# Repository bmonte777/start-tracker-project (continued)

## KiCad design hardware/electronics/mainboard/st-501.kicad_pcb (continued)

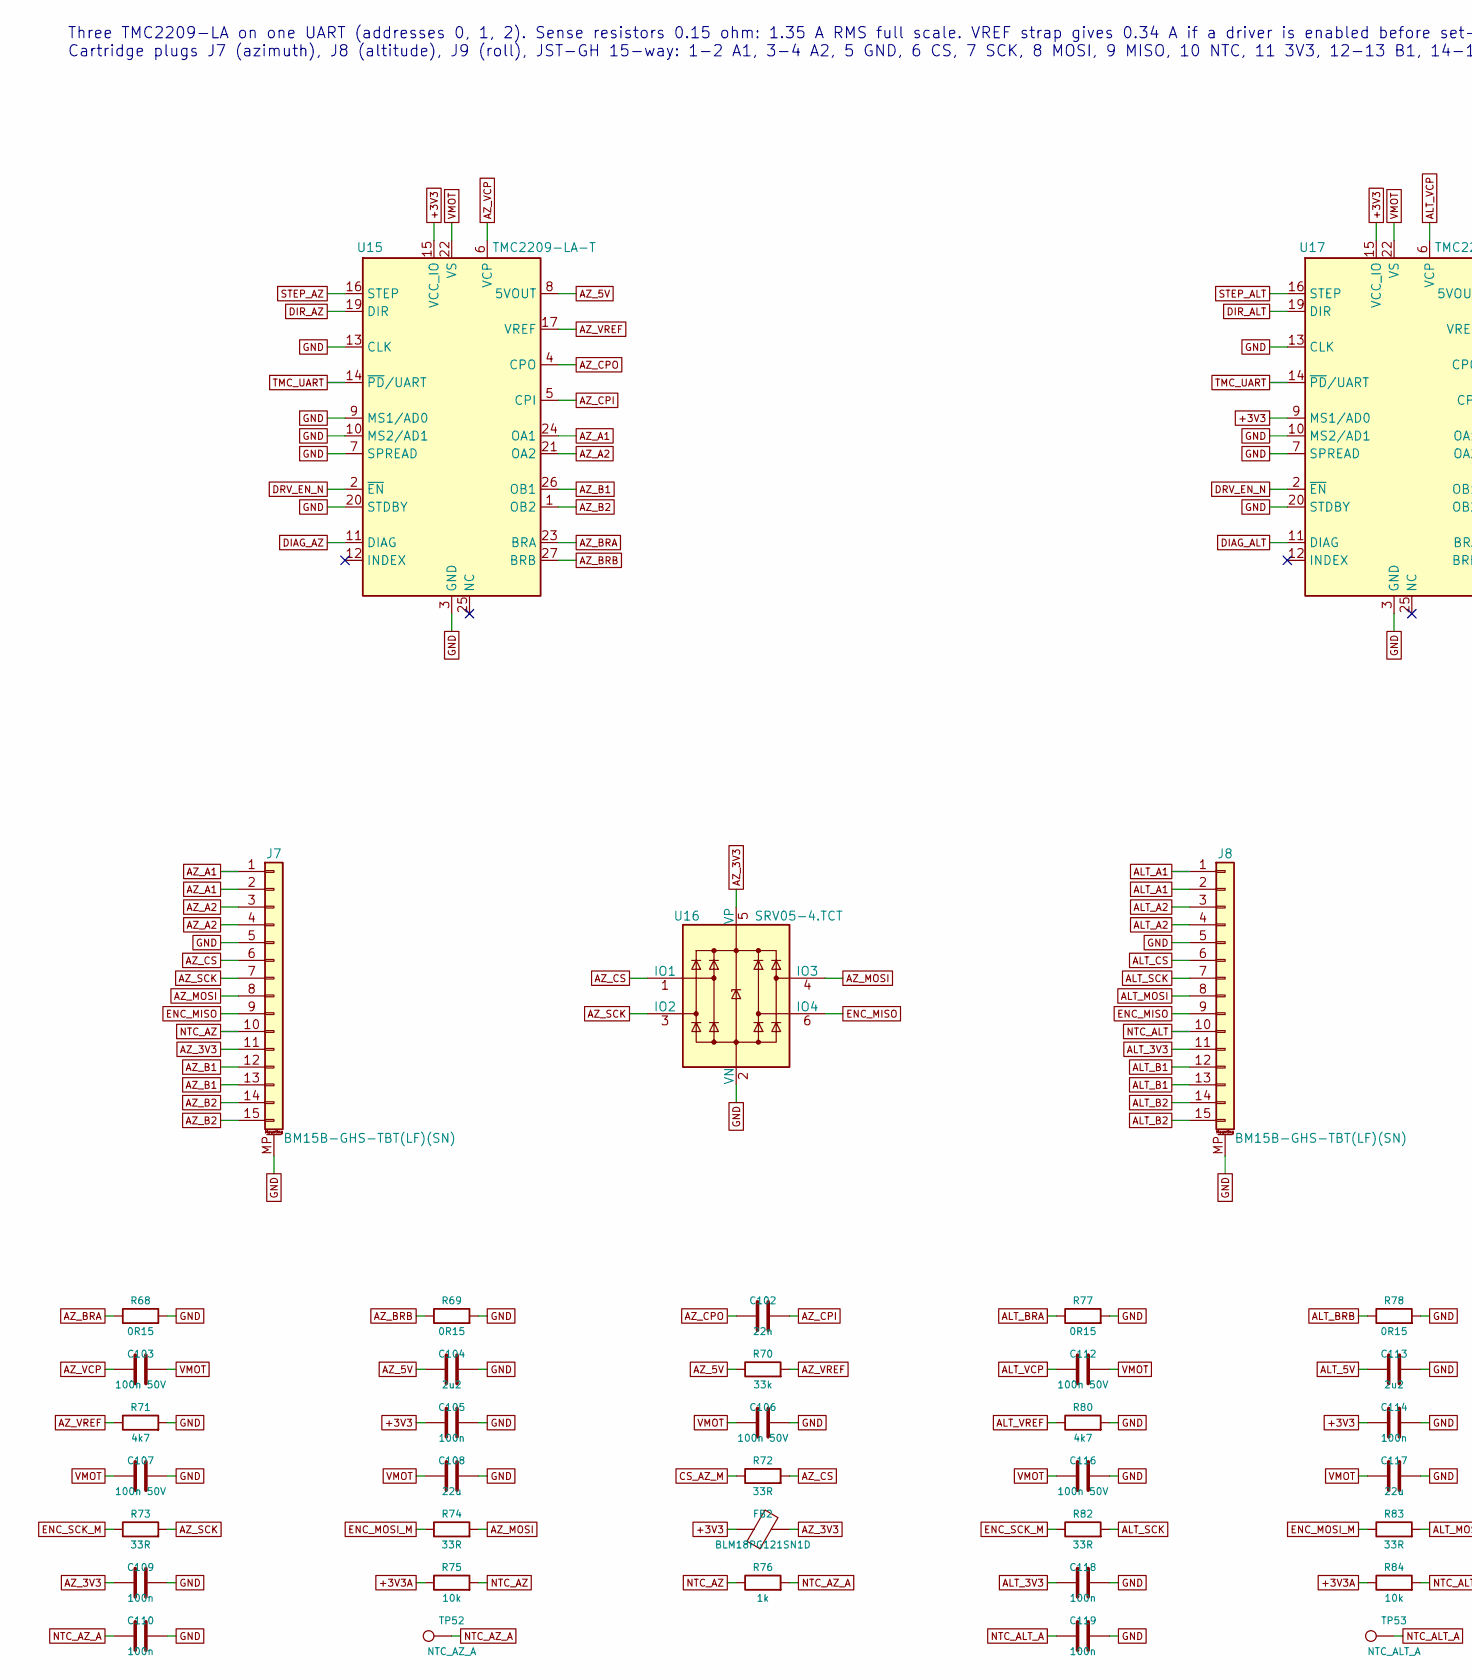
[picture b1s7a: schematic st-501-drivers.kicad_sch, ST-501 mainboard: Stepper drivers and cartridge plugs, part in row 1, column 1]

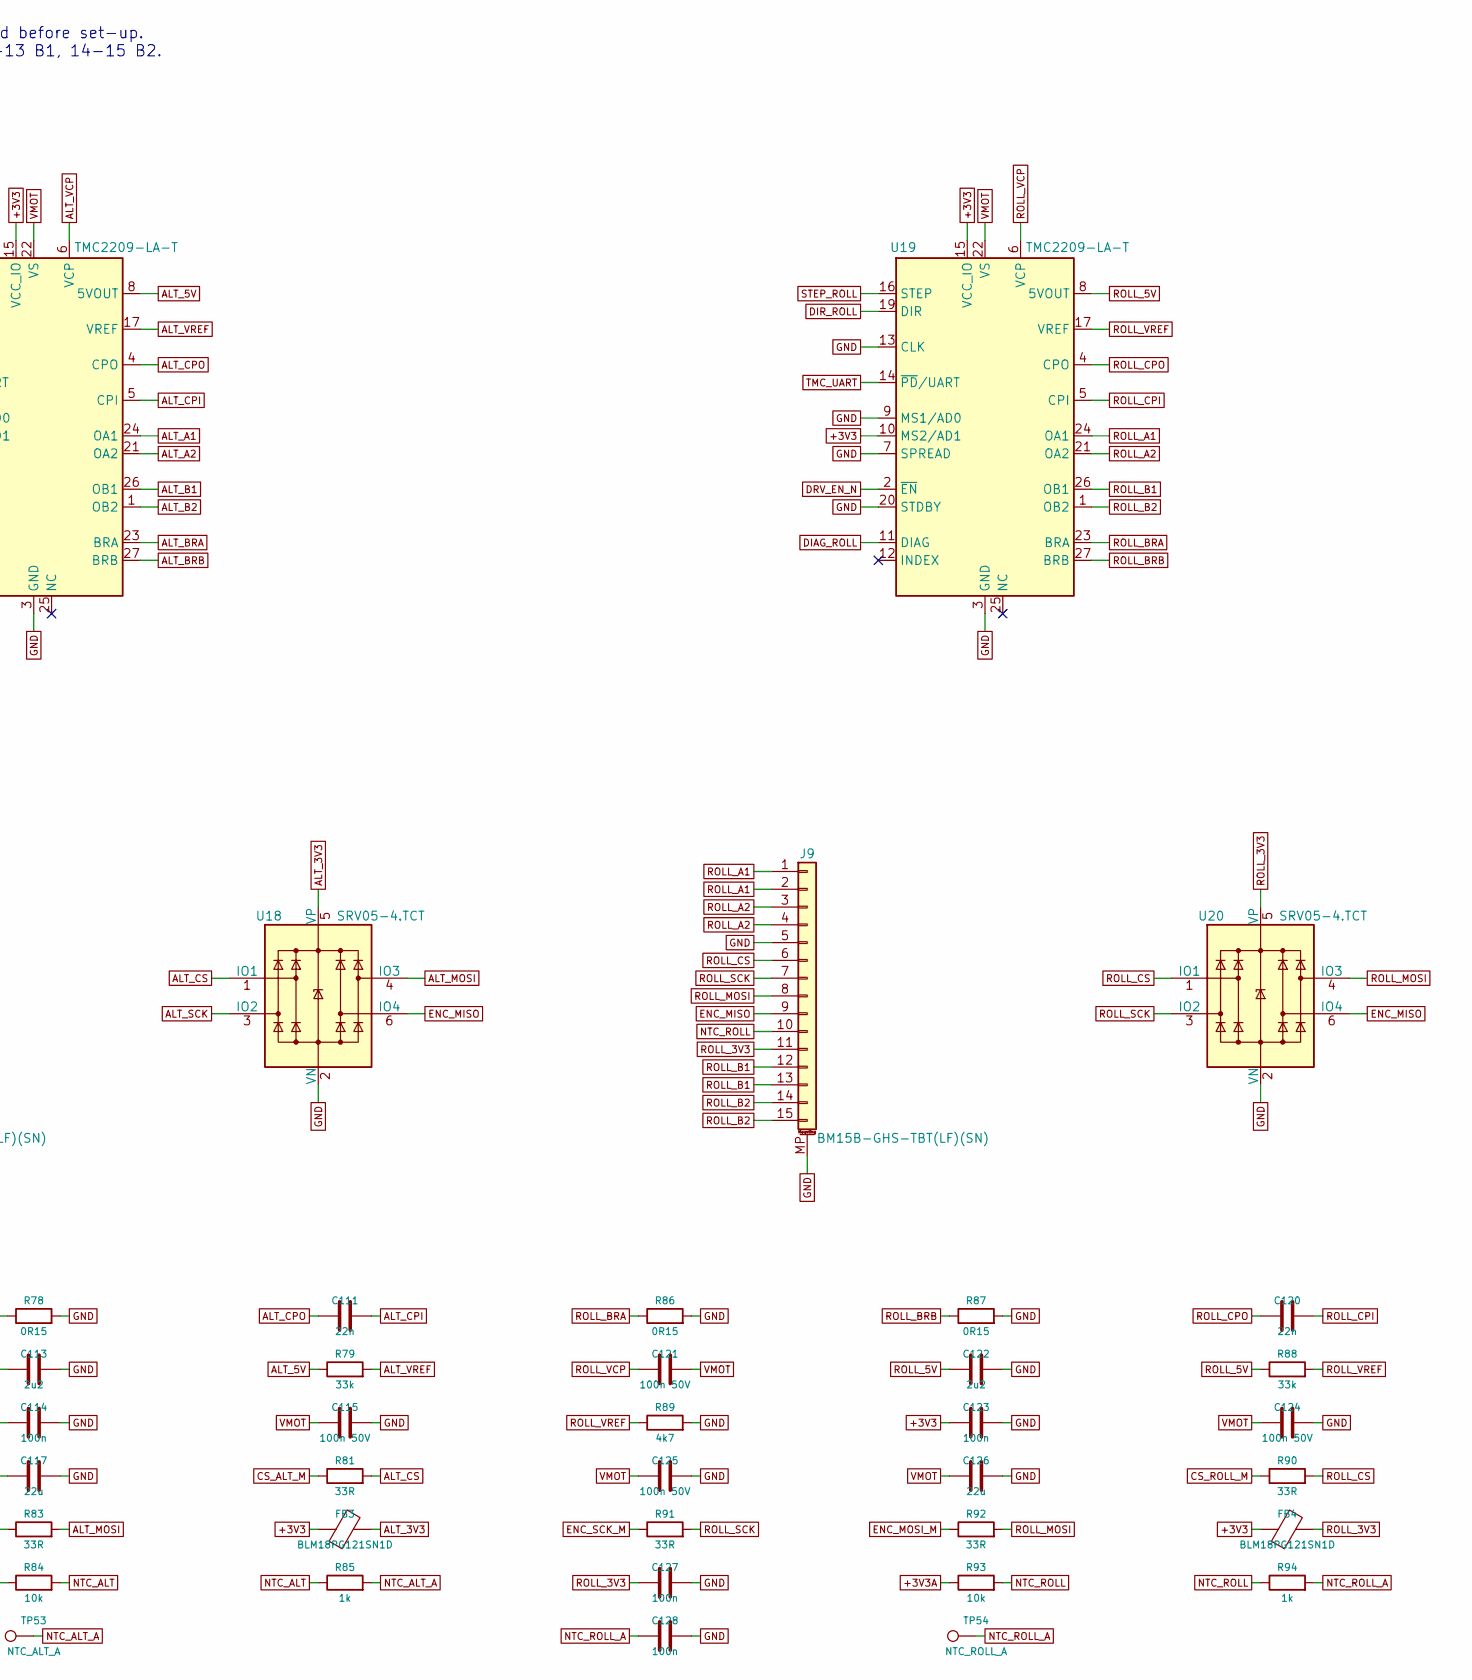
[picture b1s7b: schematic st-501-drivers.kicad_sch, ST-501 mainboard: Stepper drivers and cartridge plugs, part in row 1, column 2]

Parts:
C102, C111, C120: 22n; C_0402_1005Metric; MPN CL05B223KB5NNNC; LCSC C1532
C103, C106, C107, C112, C115, C116, C121, C124, C125: 100n 50V; C_0402_1005Metric; MPN CL05B104KB54PNC; LCSC C307331
C104, C113, C122: 2u2; C_0603_1608Metric; MPN CL10A225KO8NNNC; LCSC C23630
C105, C109, C110, C114, C118, C119, C123, C127, C128: 100n; C_0402_1005Metric; MPN CL05B104KO5NNNC; LCSC C1525
C108, C117, C126: 22u; C_0805_2012Metric; MPN CL21A226MAQNNNE; LCSC C45783
FB2, FB3, FB4: BLM18PG121SN1D; L_0603_1608Metric; MPN BLM18PG121SN1D; LCSC C14709
J7, J8, J9: BM15B-GHS-TBT(LF)(SN); JST_GH_BM15B-GHS-TBT_1x15-1MP_P1.25mm_Vertical_3D; MPN BM15B-GHS-TBT(LF)(SN); LCSC C5305069
R68, R69, R77, R78, R86, R87: 0R15; R_1206_3216Metric; MPN 0.15 ohm 1 % 0.5 W current sense
R70, R79, R88: 33k; R_0402_1005Metric; MPN 0402WGF3302TCE; LCSC C25779
R71, R80, R89: 4k7; R_0402_1005Metric; MPN 0402WGF4701TCE; LCSC C25900
R72, R73, R74, R81, R82, R83, R90, R91, R92: 33R; R_0402_1005Metric; MPN 0402WGF330JTCE; LCSC C25105
R75, R84, R93: 10k; R_0402_1005Metric; MPN 0402WGF1002TCE; LCSC C25744
R76, R85, R94: 1k; R_0402_1005Metric; MPN 0402WGF1001TCE; LCSC C11702
TP52: NTC_AZ_A; TestPoint_Pad_D1.0mm
TP53: NTC_ALT_A; TestPoint_Pad_D1.0mm
TP54: NTC_ROLL_A; TestPoint_Pad_D1.0mm
U15, U17, U19: TMC2209-LA-T; VQFN-28-1EP_5x5mm_P0.5mm_EP3.7x3.7mm_ThermalVias; MPN TMC2209-LA-T; LCSC C465949
U16, U18, U20: SRV05-4.TCT; SOT-23-6; MPN SRV05-4.TCT; LCSC C2687126

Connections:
+3V3: C105.1, C114.1, C123.1, FB2.1, FB3.1, FB4.1, U15.15 (VCC_IO), U17.9 (MS1/AD0), U17.15 (VCC_IO), U19.10 (MS2/AD1), U19.15 (VCC_IO); also elsewhere on the board
+3V3A: R75.1, R84.1, R93.1; also elsewhere on the board
ALT_3V3: C118.1, FB3.2, J8.11, U18.5 (VP)
ALT_5V: C113.1, R79.1, U17.8 (5VOUT)
ALT_A1: J8.1, J8.2, U17.24 (OA1)
ALT_A2: J8.3, J8.4, U17.21 (OA2)
ALT_B1: J8.12, J8.13, U17.26 (OB1)
ALT_B2: J8.14, J8.15, U17.1 (OB2)
ALT_BRA: R77.1, U17.23 (BRA)
ALT_BRB: R78.1, U17.27 (BRB)
ALT_CPI: C111.2, U17.5 (CPI)
ALT_CPO: C111.1, U17.4 (CPO)
ALT_CS: J8.6, R81.2, U18.1 (IO1)
ALT_MOSI: J8.8, R83.2, U18.4 (IO3)
ALT_SCK: J8.7, R82.2, U18.3 (IO2)
ALT_VCP: C112.1, U17.6 (VCP)
ALT_VREF: R79.2, R80.1, U17.17 (VREF)
AZ_3V3: C109.1, FB2.2, J7.11, U16.5 (VP)
AZ_5V: C104.1, R70.1, U15.8 (5VOUT)
AZ_A1: J7.1, J7.2, U15.24 (OA1)
AZ_A2: J7.3, J7.4, U15.21 (OA2)
AZ_B1: J7.12, J7.13, U15.26 (OB1)
AZ_B2: J7.14, J7.15, U15.1 (OB2)
AZ_BRA: R68.1, U15.23 (BRA)
AZ_BRB: R69.1, U15.27 (BRB)
AZ_CPI: C102.2, U15.5 (CPI)
AZ_CPO: C102.1, U15.4 (CPO)
AZ_CS: J7.6, R72.2, U16.1 (IO1)
AZ_MOSI: J7.8, R74.2, U16.4 (IO3)
AZ_SCK: J7.7, R73.2, U16.3 (IO2)
AZ_VCP: C103.1, U15.6 (VCP)
AZ_VREF: R70.2, R71.1, U15.17 (VREF)
CS_ALT_M: R81.1; also elsewhere on the board
CS_AZ_M: R72.1; also elsewhere on the board
CS_ROLL_M: R90.1; also elsewhere on the board
DIAG_ALT: U17.11 (DIAG); also elsewhere on the board
DIAG_AZ: U15.11 (DIAG); also elsewhere on the board
DIAG_ROLL: U19.11 (DIAG); also elsewhere on the board
DIR_ALT: U17.19 (DIR); also elsewhere on the board
DIR_AZ: U15.19 (DIR); also elsewhere on the board
DIR_ROLL: U19.19 (DIR); also elsewhere on the board
DRV_EN_N: U15.2 (~EN), U17.2 (~EN), U19.2 (~EN); also elsewhere on the board
ENC_MISO: J7.9, J8.9, J9.9, U16.6 (IO4), U18.6 (IO4), U20.6 (IO4); also elsewhere on the board
ENC_MOSI_M: R74.1, R83.1, R92.1; also elsewhere on the board
ENC_SCK_M: R73.1, R82.1, R91.1; also elsewhere on the board
GND: C104.2, C105.2, C106.2, C107.2, C108.2, C109.2, C110.2, C113.2, C114.2, C115.2, C116.2, C117.2, C118.2, C119.2, C122.2, C123.2, C124.2, C125.2, C126.2, C127.2, C128.2, J7.5, J7.MP (MountPin), J8.5, J8.MP (MountPin), J9.5, J9.MP (MountPin), R68.2, R69.2, R71.2, R77.2, R78.2, R80.2, R86.2, R87.2, R89.2, U15.3 (GND), U15.7 (SPREAD), U15.9 (MS1/AD0), U15.10 (MS2/AD1), U15.13 (CLK), U15.18 (GND), U15.20 (STDBY), U15.29 (GND), U16.2 (VN), U17.3 (GND), U17.7 (SPREAD), U17.10 (MS2/AD1), U17.13 (CLK), U17.18 (GND), U17.20 (STDBY), U17.29 (GND), U18.2 (VN), U19.3 (GND), U19.7 (SPREAD), U19.9 (MS1/AD0), U19.13 (CLK), U19.18 (GND), U19.20 (STDBY), U19.29 (GND), U20.2 (VN); also elsewhere on the board
NTC_ALT: J8.10, R84.2, R85.1
NTC_ALT_A: C119.1, R85.2, TP53.1; also elsewhere on the board
NTC_AZ: J7.10, R75.2, R76.1
NTC_AZ_A: C110.1, R76.2, TP52.1; also elsewhere on the board
NTC_ROLL: J9.10, R93.2, R94.1
NTC_ROLL_A: C128.1, R94.2, TP54.1; also elsewhere on the board
ROLL_3V3: C127.1, FB4.2, J9.11, U20.5 (VP)
ROLL_5V: C122.1, R88.1, U19.8 (5VOUT)
ROLL_A1: J9.1, J9.2, U19.24 (OA1)
ROLL_A2: J9.3, J9.4, U19.21 (OA2)
ROLL_B1: J9.12, J9.13, U19.26 (OB1)
ROLL_B2: J9.14, J9.15, U19.1 (OB2)
ROLL_BRA: R86.1, U19.23 (BRA)
ROLL_BRB: R87.1, U19.27 (BRB)
ROLL_CPI: C120.2, U19.5 (CPI)
ROLL_CPO: C120.1, U19.4 (CPO)
ROLL_CS: J9.6, R90.2, U20.1 (IO1)
ROLL_MOSI: J9.8, R92.2, U20.4 (IO3)
ROLL_SCK: J9.7, R91.2, U20.3 (IO2)
ROLL_VCP: C121.1, U19.6 (VCP)
ROLL_VREF: R88.2, R89.1, U19.17 (VREF)
STEP_ALT: U17.16 (STEP); also elsewhere on the board
STEP_AZ: U15.16 (STEP); also elsewhere on the board
STEP_ROLL: U19.16 (STEP); also elsewhere on the board
TMC_UART: U15.14 (~PD/UART), U17.14 (~PD/UART), U19.14 (~PD/UART); also elsewhere on the board
VMOT: C103.2, C106.1, C107.1, C108.1, C112.2, C115.1, C116.1, C117.1, C121.2, C124.1, C125.1, C126.1, U15.22 (VS), U15.28 (VS), U17.22 (VS), U17.28 (VS), U19.22 (VS), U19.28 (VS); also elsewhere on the board

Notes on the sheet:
Three TMC2209-LA on one UART (addresses 0, 1, 2). Sense resistors 0.15 ohm: 1.35 A RMS full scale. VREF strap gives 0.34 A if a driver is enabled before set-up. Cartridge plugs J7 (azimuth), J8 (altitude), J9 (roll), JST-GH 15-way: 1-2 A1, 3-4 A2, 5 GND, 6 CS, 7 SCK, 8 MOSI, 9 MISO, 10 NTC, 11 3V3,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

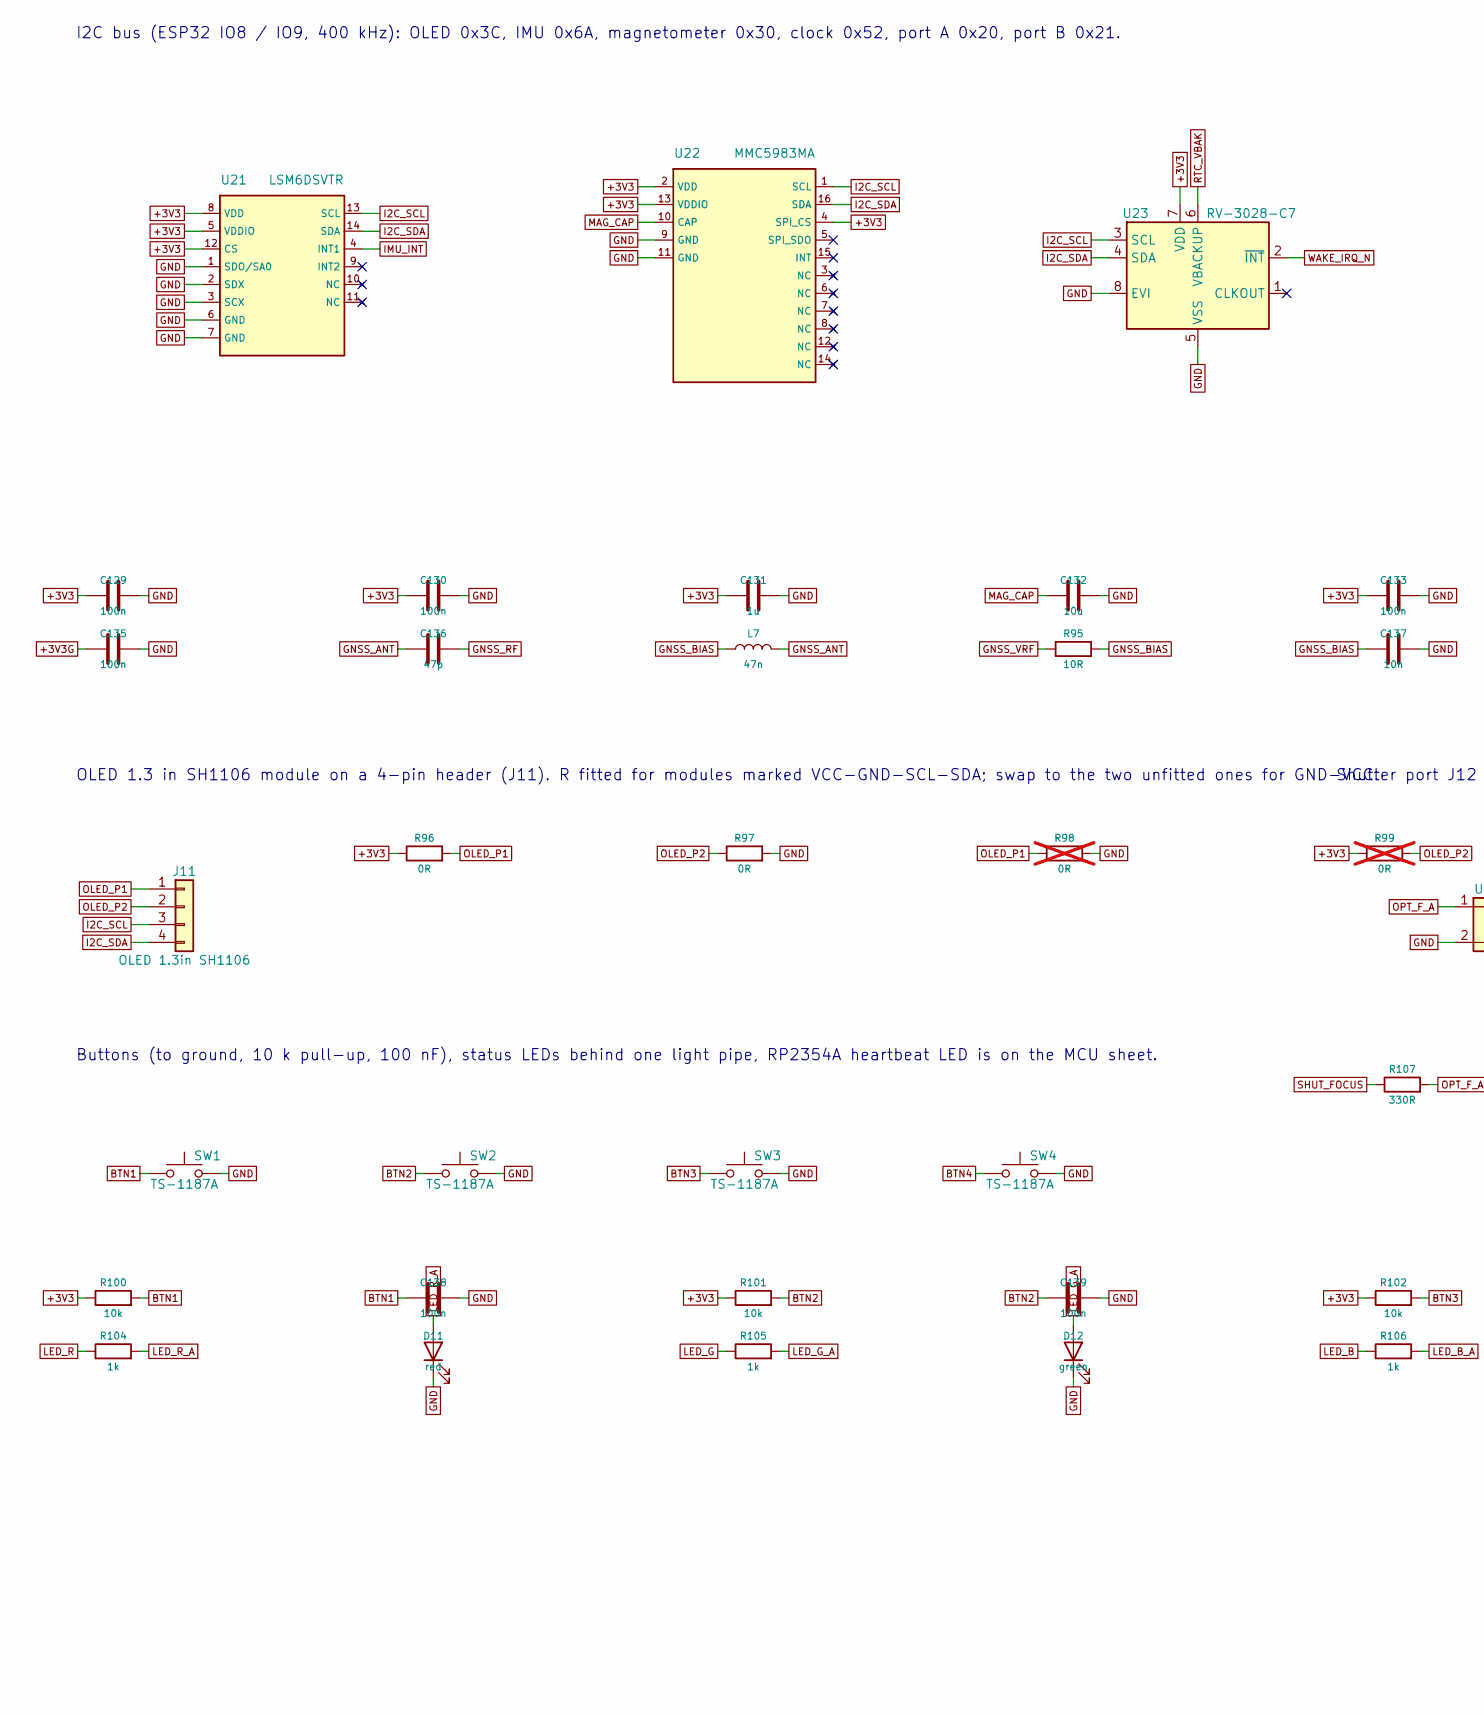
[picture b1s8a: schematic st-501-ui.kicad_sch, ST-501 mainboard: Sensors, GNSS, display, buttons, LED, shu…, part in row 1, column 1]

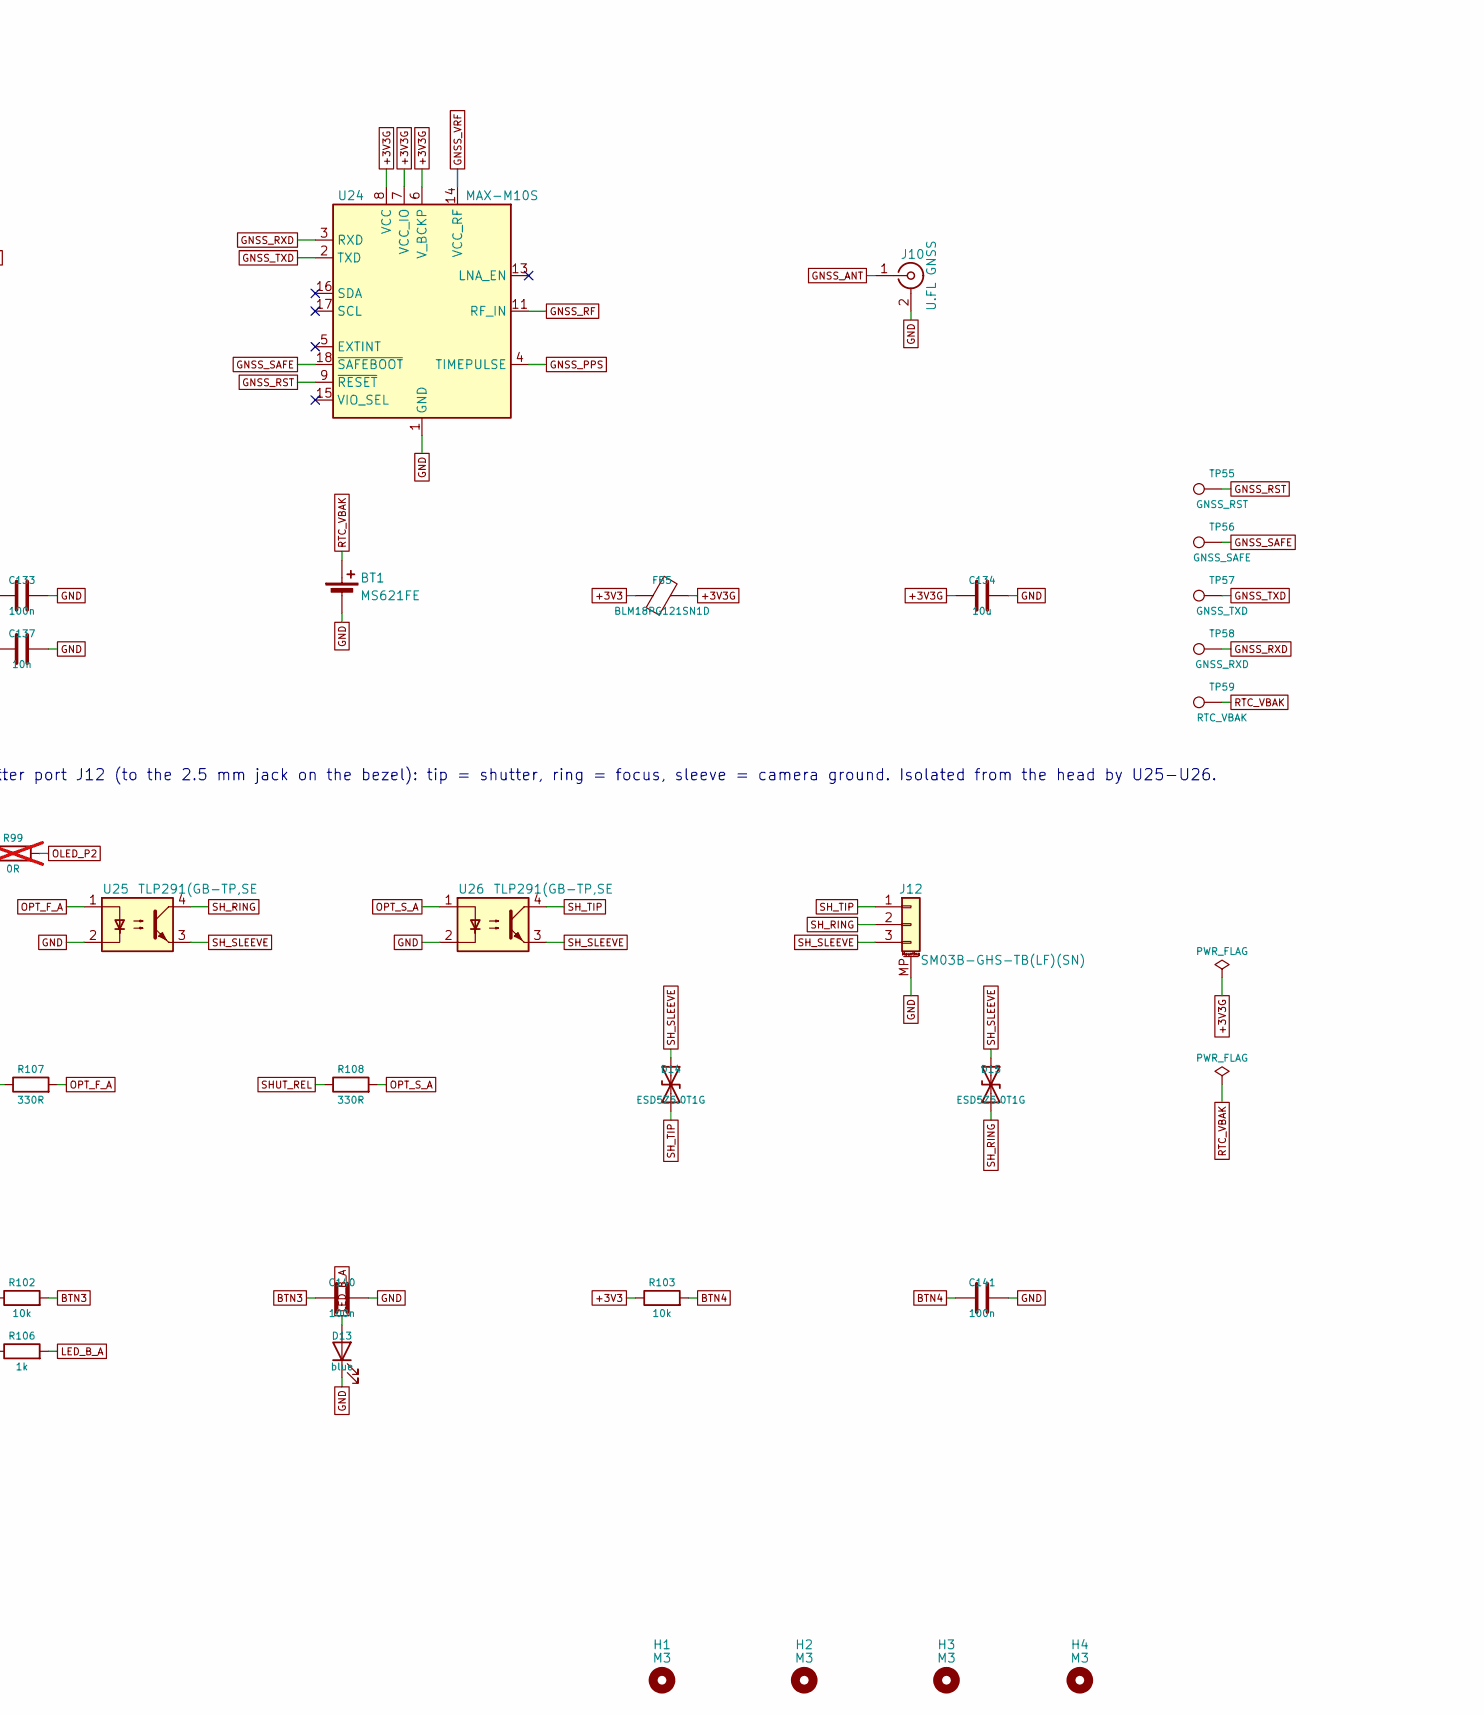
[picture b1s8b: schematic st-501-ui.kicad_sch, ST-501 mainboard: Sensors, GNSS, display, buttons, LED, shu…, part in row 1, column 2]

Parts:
BT1: MS621FE; BatteryHolder_Seiko_MS621F; MPN MS621FE-FL11E
C129, C130, C133, C135, C138, C139, C140, C141: 100n; C_0402_1005Metric; MPN CL05B104KO5NNNC; LCSC C1525
C131: 1u; C_0402_1005Metric; MPN CL05A105KA5NQNC; LCSC C52923
C132, C134: 10u; C_0603_1608Metric; MPN CL10A106KP8NNNC; LCSC C19702
C136: 47p; C_0402_1005Metric; MPN 0402CG470J500NT; LCSC C1567
C137: 10n; C_0402_1005Metric; MPN CL05B103KB5NNNC; LCSC C15195
D11: red; LED_0603_1608Metric; MPN KT-0603R; LCSC C2286
D12: green; LED_0603_1608Metric; MPN 19-217/GHC-YR1S2/3T; LCSC C72043
D13: blue; LED_0603_1608Metric; MPN 19-217/BHC-ZL1M2RY/3T; LCSC C72041
D14, D15: ESD5Z5.0T1G; D_SOD-523; MPN ESD5Z5.0T1G
FB5: BLM18PG121SN1D; L_0603_1608Metric; MPN BLM18PG121SN1D; LCSC C14709
H1, H2, H3, H4: M3; MountingHole_3.2mm_M3_ISO7380
J10: U.FL GNSS; U.FL_Hirose_U.FL-R-SMT-1_Vertical; MPN U.FL-R-SMT-1(80); LCSC C88374
J11: OLED 1.3in SH1106; PinHeader_1x04_P2.54mm_Vertical
J12: SM03B-GHS-TB(LF)(SN); JST_GH_SM03B-GHS-TB_1x03-1MP_P1.25mm_Horizontal; MPN SM03B-GHS-TB(LF)(SN); LCSC C514175
L7: 47n; L_0402_1005Metric; MPN LQG15HS47NJ02D; LCSC C97998
R95: 10R; R_0402_1005Metric; MPN 0402WGF100JTCE; LCSC C25077
R96, R97: 0R; R_0402_1005Metric; MPN 0402WGF0000TCE; LCSC C17168
R98, R99: 0R; R_0402_1005Metric; MPN 0402WGF0000TCE; LCSC C17168; not fitted
R100, R101, R102, R103: 10k; R_0402_1005Metric; MPN 0402WGF1002TCE; LCSC C25744
R104, R105, R106: 1k; R_0402_1005Metric; MPN 0402WGF1001TCE; LCSC C11702
R107, R108: 330R; R_0402_1005Metric; MPN 0402WGF3300TCE; LCSC C25104
SW1, SW2, SW3, SW4: TS-1187A; SW_Push_1P1T_XKB_TS-1187A; MPN TS-1187A-B-A-B; LCSC C318884
TP55: GNSS_RST; TestPoint_Pad_D1.0mm
TP56: GNSS_SAFE; TestPoint_Pad_D1.0mm
TP57: GNSS_TXD; TestPoint_Pad_D1.0mm
TP58: GNSS_RXD; TestPoint_Pad_D1.0mm
TP59: RTC_VBAK; TestPoint_Pad_D1.0mm
U21: LSM6DSVTR; LGA-14_3x2.5mm_P0.5mm_LayoutBorder3x4y; MPN LSM6DSVTR
U22: MMC5983MA; LGA-16_3x3mm_P0.5mm; MPN MMC5983MA; LCSC C404329
U23: RV-3028-C7; MicroCrystal_C7_SON-8_1.5x3.2mm_P0.9mm; MPN RV-3028-C7 32.768kHz 1ppm TA QC
U24: MAX-M10S; ublox_MAX; MPN MAX-M10S-00B
U25, U26: TLP291(GB-TP,SE; SOIC-4_4.55x2.6mm_P1.27mm; MPN TLP291(GB-TP,SE; LCSC C55144

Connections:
+3V3: C129.1, C130.1, C131.1, C133.1, FB5.1, R96.1, R99.1, R100.1, R101.1, R102.1, R103.1, U21.5 (VDDIO), U21.8 (VDD), U21.12 (CS), U22.2 (VDD), U22.4 (SPI_CS), U22.13 (VDDIO), U23.7 (VDD); also elsewhere on the board
+3V3G: C134.1, C135.1, FB5.2, U24.6 (V_BCKP), U24.7 (VCC_IO), U24.8 (VCC)
BTN1: C138.1, R100.2, SW1.1; also elsewhere on the board
BTN2: C139.1, R101.2, SW2.1; also elsewhere on the board
BTN3: C140.1, R102.2, SW3.1; also elsewhere on the board
BTN4: C141.1, R103.2, SW4.1; also elsewhere on the board
GND: BT1.2 (-), C129.2, C130.2, C131.2, C132.2, C133.2, C134.2, C135.2, C137.2, C138.2, C139.2, C140.2, C141.2, D11.1 (K), D12.1 (K), D13.1 (K), J10.2 (Ext), J12.MP (MountPin), R97.2, R98.2, SW1.2, SW2.2, SW3.2, SW4.2, U21.1 (SDO/SA0), U21.2 (SDX), U21.3 (SCX), U21.6 (GND), U21.7 (GND), U22.9 (GND), U22.11 (GND), U23.5 (VSS), U23.8 (EVI), U24.1 (GND), U24.10 (GND), U24.12 (GND), U25.2, U26.2; also elsewhere on the board
GNSS_ANT: C136.1, J10.1 (In), L7.2
GNSS_BIAS: C137.1, L7.1, R95.2
GNSS_PPS: U24.4 (TIMEPULSE); also elsewhere on the board
GNSS_RF: C136.2, U24.11 (RF_IN)
GNSS_RST: TP55.1, U24.9 (~RESET)
GNSS_RXD: TP58.1, U24.3 (RXD); also elsewhere on the board
GNSS_SAFE: TP56.1, U24.18 (~SAFEBOOT)
GNSS_TXD: TP57.1, U24.2 (TXD); also elsewhere on the board
GNSS_VRF: R95.1, U24.14 (VCC_RF)
I2C_SCL: J11.3, U21.13 (SCL), U22.1 (SCL), U23.3 (SCL); also elsewhere on the board
I2C_SDA: J11.4, U21.14 (SDA), U22.16 (SDA), U23.4 (SDA); also elsewhere on the board
IMU_INT: U21.4 (INT1); also elsewhere on the board
LED_B: R106.1; also elsewhere on the board
LED_B_A: D13.2 (A), R106.2
LED_G: R105.1; also elsewhere on the board
LED_G_A: D12.2 (A), R105.2
LED_R: R104.1; also elsewhere on the board
LED_R_A: D11.2 (A), R104.2
MAG_CAP: C132.1, U22.10 (CAP)
OLED_P1: J11.1, R96.2, R98.1
OLED_P2: J11.2, R97.1, R99.2
OPT_F_A: R107.2, U25.1
OPT_S_A: R108.2, U26.1
RTC_VBAK: BT1.1 (+), TP59.1, U23.6 (VBACKUP)
SHUT_FOCUS: R107.1; also elsewhere on the board
SHUT_REL: R108.1; also elsewhere on the board
SH_RING: D15.1 (A1), J12.2, U25.4
SH_SLEEVE: D14.2 (A2), D15.2 (A2), J12.3, U25.3, U26.3
SH_TIP: D14.1 (A1), J12.1, U26.4
WAKE_IRQ_N: U23.2 (~INT); also elsewhere on the board

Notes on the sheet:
I2C bus (ESP32 IO8 / IO9, 400 kHz): OLED 0x3C, IMU 0x6A, magnetometer 0x30, clock 0x52, port A 0x20, port B 0x21.
OLED 1.3 in SH1106 module on a 4-pin header (J11). R fitted for modules marked VCC-GND-SCL-SDA; swap to the two unfitted ones for GND-VCC.
Buttons (to ground, 10 k pull-up, 100 nF), status LEDs behind one light pipe, RP2354A heartbeat LED is on the MCU sheet.
Shutter port J12 (to the 2.5 mm jack on the bezel): tip = shutter, ring = focus, sleeve = camera ground. Isolated from the head by U25-U26.

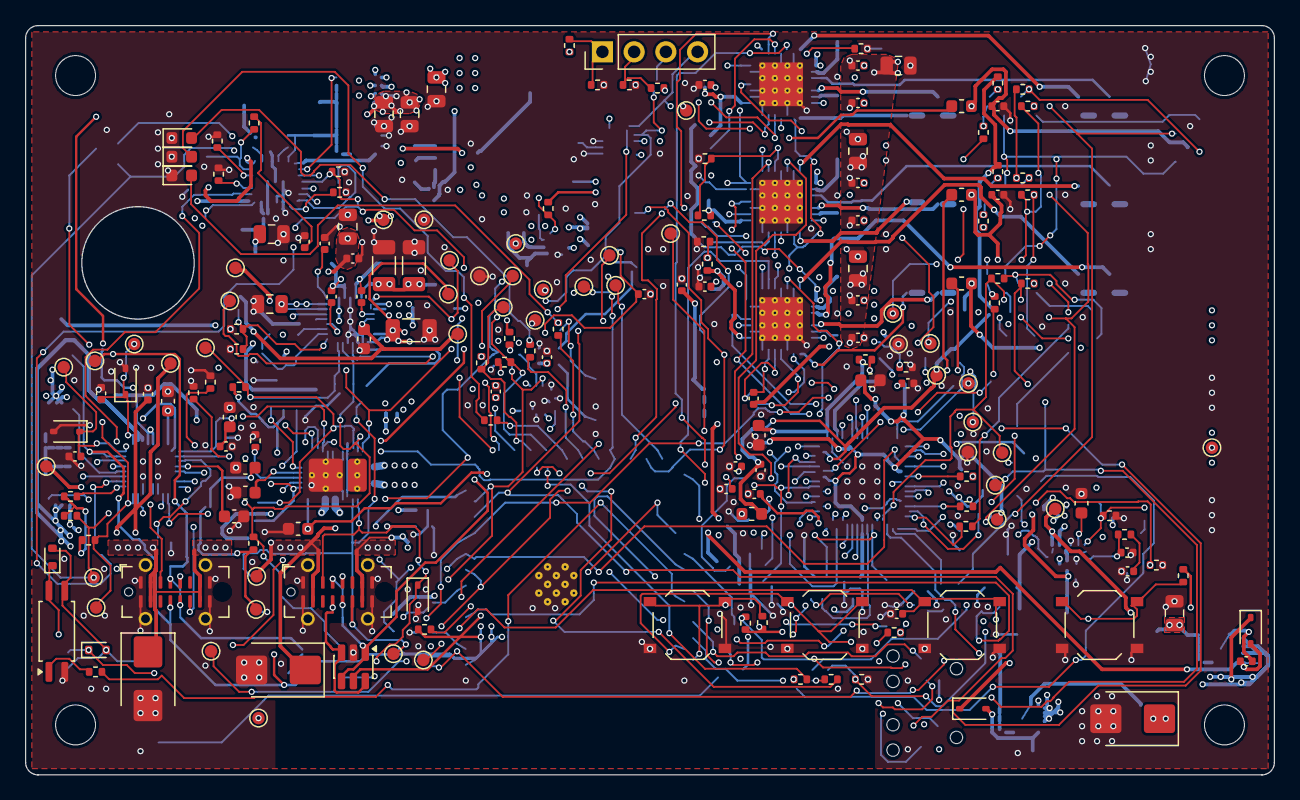
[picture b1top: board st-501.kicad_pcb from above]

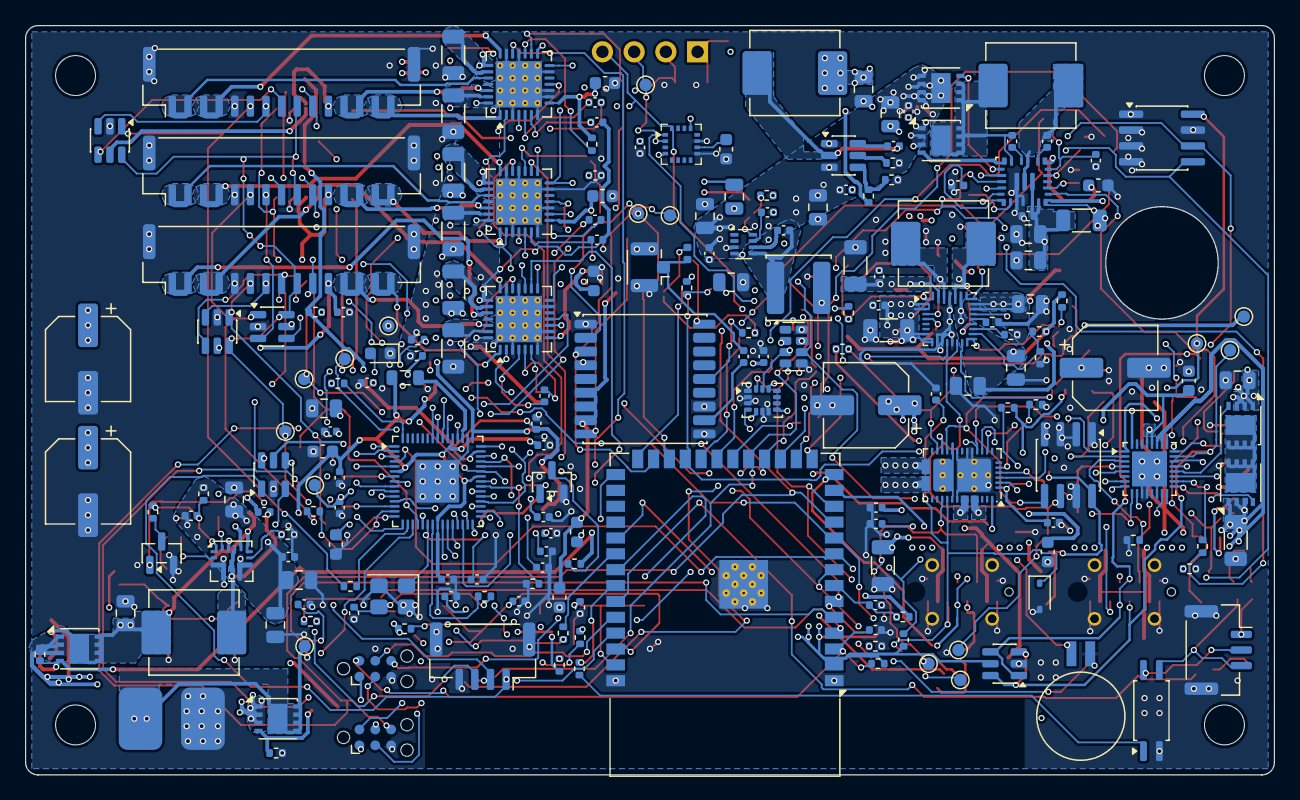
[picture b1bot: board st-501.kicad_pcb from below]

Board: 6 copper layers, 100.0 x 60.0 mm, 391 parts (202 on the bottom side), 229 nets.

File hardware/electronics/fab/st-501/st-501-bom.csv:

Comment,Designator,Footprint,LCSC Part #,MPN,Qty
MS621FE,BT1,BatteryHolder_Seiko_MS621F,,MS621FE-FL11E,1
100n,"C1,C28,C29,C30,C46,C54,C60,C79,C81,C89,C90,C91,C92,C93,C94,C95,C96,C97,C98,C99,C101,C105,C109,C110,C114,C118,C119,C123,C127,C128,C129,C130,C133,C135,C138,C139,C140,C141",C_0402_1005Metric,C1525,CL05B104KO5NNNC,38
47n,"C2,C3",C_0402_1005Metric,,47 nF X7R 25 V 0402,2
4u7,"C4,C31,C85,C86,C87,C88",C_0603_1608Metric,C19666,CL10A475KO8NNNC,6
1n,C5,C_0402_1005Metric,C1523,0402B102K500NT,1
10u 50V,"C6,C7,C9,C10,C11,C23,C50",C_1206_3216Metric,C13585,CL31A106KBHNNNE,7
100n 50V,"C8,C12,C16,C24,C38,C42,C51,C57,C62,C65,C66,C76,C103,C106,C107,C112,C115,C116,C121,C124,C125",C_0402_1005Metric,C307331,CL05B104KB54PNC,21
22u,"C13,C14,C15,C17,C18,C35,C36,C37,C39,C40,C41,C43,C56,C58,C59,C61,C63,C64,C71,C72,C73,C74,C75,C80,C108,C117,C126",C_0805_2012Metric,C45783,CL21A226MAQNNNE,27
47u 25V,C19,CP_Elec_6.3x5.8,,47 uF 25 V polymer,1
10u,"C20,C21,C22,C25,C44,C45,C47,C48,C132,C134",C_0603_1608Metric,C19702,CL10A106KP8NNNC,10
220p,"C26,C27,C52,C53",C_0402_1005Metric,C1530,0402B221K500NT,4
10n,"C32,C33,C137",C_0402_1005Metric,C15195,CL05B103KB5NNNC,3
100p,C34,C_0402_1005Metric,C1546,CL05C101JB5NNNC,1
100u 10V,C49,CP_Elec_6.3x5.8,,100 uF 10 V polymer,1
22n,"C55,C102,C111,C120",C_0402_1005Metric,C1532,CL05B223KB5NNNC,4
2u2,"C67,C104,C113,C122",C_0603_1608Metric,C23630,CL10A225KO8NNNC,4
15n,C68,C_0402_1005Metric,,15 nF X7R 50 V 0402,1
39p,C69,C_0402_1005Metric,,39 pF C0G 50 V 0402,1
27p,"C70,C83,C84",C_0402_1005Metric,C1557,CL05C270JB5NNNC,3
100u 25V,"C77,C78",CP_Elec_6.3x7.7,,100 uF 25 V polymer hybrid,2
1u,"C82,C100,C131",C_0402_1005Metric,C52923,CL05A105KA5NQNC,3
47p,C136,C_0402_1005Metric,C1567,0402CG470J500NT,1
BZT52C12S,"D1,D9",D_SOD-323,C14643,BZT52C12S,2
SMBJ12A-TR,D2,D_SMB,C133677,SMBJ12A-TR,1
SMBJ24A,"D3,D6",D_SMB,C353373,SMBJ24A,2
PESD24VS1UB,"D4,D5,D7,D8",D_SOD-323,,PESD24VS1UB,4
green,"D10,D12",LED_0603_1608Metric,C72043,19-217/GHC-YR1S2/3T,2
red,D11,LED_0603_1608Metric,C2286,KT-0603R,1
blue,D13,LED_0603_1608Metric,C72041,19-217/BHC-ZL1M2RY/3T,1
ESD5Z5.0T1G,"D14,D15",D_SOD-523,,ESD5Z5.0T1G,2
BLM18PG121SN1D,"FB1,FB2,FB3,FB4,FB5",L_0603_1608Metric,C14709,BLM18PG121SN1D,5
SM04B-GHS-TB(LF)(SN),J2,JST_GH_SM04B-GHS-TB_1x04-1MP_P1.25mm_Horizontal,C189895,SM04B-GHS-TB(LF)(SN),1
USB-C A,J3,USB_C_Receptacle_G-Switch_GT-USB-7051x,C2843970,GT-USB-7051A,1
USB-C B,J4,USB_C_Receptacle_G-Switch_GT-USB-7051x,C2843970,GT-USB-7051A,1
BM15B-GHS-TBT(LF)(SN),"J7,J8,J9",JST_GH_BM15B-GHS-TBT_1x15-1MP_P1.25mm_Vertical_3D,C5305069,BM15B-GHS-TBT(LF)(SN),3
U.FL GNSS,J10,U.FL_Hirose_U.FL-R-SMT-1_Vertical,C88374,U.FL-R-SMT-1(80),1
SM03B-GHS-TB(LF)(SN),J12,JST_GH_SM03B-GHS-TB_1x03-1MP_P1.25mm_Horizontal,C514175,SM03B-GHS-TB(LF)(SN),1
2u2,L1,L_Sunlord_MWSA0603S,,MWSC0630H2R2MT,1
4u7,"L2,L4,L5",L_Sunlord_MWSA0603S,C2991788,MWSC0630H4R7MT,3
6u8,L3,L_Sunlord_SWPA5040S,C36411,SWPA5040S6R8MT,1
3u3,L6,L_0805_2012Metric,,AOTA-B201610S3R3-101-T,1
47n,L7,L_0402_1005Metric,C97998,LQG15HS47NJ02D,1
AON7403,"Q1,Q6",DFN-8-1EP_3x3mm_P0.65mm_EP1.55x2.4mm,C5310961,AON7403,2
AON7400A,"Q2,Q3,Q4,Q5",DFN-8-1EP_3x3mm_P0.65mm_EP1.55x2.4mm,C85734,AON7400A,4
2N7002,"Q7,Q8",SOT-23,C8545,2N7002,2
100k,"R1,R7,R28,R35,R36,R39,R42,R44,R49,R50,R51",R_0402_1005Metric,C25741,0402WGF1003TCE,11
100R,"R2,R3,R15,R59,R60",R_0402_1005Metric,C25076,0402WGF1000TCE,5
1k,"R4,R62,R64,R65,R67,R76,R85,R94,R104,R105,R106",R_0402_1005Metric,C11702,0402WGF1001TCE,11
4k7,"R5,R6,R71,R80,R89",R_0402_1005Metric,C25900,0402WGF4701TCE,5
33k,"R8,R70,R79,R88",R_0402_1005Metric,C25779,0402WGF3302TCE,4
8k2,R9,R_0402_1005Metric,C25924,0402WGF8201TCE,1
5k23,R10,R_0402_1005Metric,C477746,RC0402FR-075K23L,1
30k1,R11,R_0402_1005Metric,C138009,RC0402FR-0730K1L,1
10k,"R12,R13,R16,R19,R22,R30,R38,R41,R43,R53,R54,R57,R58,R61,R66,R75,R84,R93,R100,R101,R102,R103",R_0402_1005Metric,C25744,0402WGF1002TCE,22
26k7,R14,R_0402_1005Metric,,RC0402FR-0726K7L,1
0R,"R17,R18,R33,R34,R96,R97",R_0402_1005Metric,C17168,0402WGF0000TCE,6
3k3,"R20,R21,R31,R32",R_0402_1005Metric,C25890,0402WGF3301TCE,4
0R01,R23,R_1206_3216Metric,,0.010 ohm 1 % 1 W current sense,1
49k9,R24,R_0402_1005Metric,C25897,0402WGF4992TCE,1
6k19,R25,R_0402_1005Metric,,RC0402FR-076K19L,1
44k2,R26,R_0402_1005Metric,,RC0402FR-0744K2L,1
20k,R27,R_0402_1005Metric,C25765,0402WGF2002TCE,1
31k6,R37,R_0402_1005Metric,C276265,RC0402FR-0731K6L,1
54k9,R40,R_0402_1005Metric,,RC0402FR-0754K9L,1
84k5,R45,R_0402_1005Metric,,RC0402FR-0784K5L,1
365k,R46,R_0402_1005Metric,,RC0402FR-07365KL,1
23k2,R47,R_0402_1005Metric,,RC0402FR-0723K2L,1
36k5,R48,R_0402_1005Metric,,RC0402FR-0736K5L,1
15k,R52,R_0402_1005Metric,C25756,0402WGF1502TCE,1
2k2,"R55,R56",R_0402_1005Metric,C25879,0402WGF2201TCE,2
33R,"R63,R72,R73,R74,R81,R82,R83,R90,R91,R92",R_0402_1005Metric,C25105,0402WGF330JTCE,10
0R15,"R68,R69,R77,R78,R86,R87",R_1206_3216Metric,,0.15 ohm 1 % 0.5 W current sense,6
10R,R95,R_0402_1005Metric,C25077,0402WGF100JTCE,1
330R,"R107,R108",R_0402_1005Metric,C25104,0402WGF3300TCE,2
TS-1187A,"SW1,SW2,SW3,SW4",SW_Push_1P1T_XKB_TS-1187A,C318884,TS-1187A-B-A-B,4
SRV05-4.TCT,"U1,U5,U9,U16,U18,U20",SOT-23-6,C2687126,SRV05-4.TCT,6
BQ25792RQMR,U2,Texas_RQM0029A_VQFN-29_4x4mm_P0.4mm,C2862876,BQ25792RQMR,1
TPS25751DREFR,U3,Texas_REF0038A_WQFN-38-2EP_6x4mm_P0.4,,TPS25751DREFR,1
CAT24C512WI-GT3,"U4,U8",SOIC-8_3.9x4.9mm_P1.27mm,C79986,CAT24C512WI-GT3,2
TPS25752ARSMR,U6,VQFN-32-1EP_4x4mm_P0.4mm_EP2.8x2.8mm,,TPS25752ARSMR,1
TPS55288RPMR,U7,Texas_RPM0026A_VQFN-HR-26_3.5x4mm,,TPS55288RPMR,1
TPS62932DRLR,U10,SOT-583-8,C3032935,TPS62932DRLR,1
TPS563201DDCR,U11,TSOT-23-6,C116592,TPS563201DDCR,1
TPS61288RQQR,U12,Texas_VQFN-HR-20_3x2.5mm_P0.5mm_RQQ0011A,C5219223,TPS61288RQQR,1
ESP32-S3-WROOM-1-N16R8,U13,ESP32-S3-WROOM-1_BodyCourtyard,C2913202,ESP32-S3-WROOM-1-N16R8,1
RP2354A,U14,QFN-60-1EP_7x7mm_P0.4mm_EP3.4x3.4mm,C41378174,RP2354A,1
TMC2209-LA-T,"U15,U17,U19",VQFN-28-1EP_5x5mm_P0.5mm_EP3.7x3.7mm_ThermalVias,C465949,TMC2209-LA-T,3
LSM6DSVTR,U21,LGA-14_3x2.5mm_P0.5mm_LayoutBorder3x4y,,LSM6DSVTR,1
MMC5983MA,U22,LGA-16_3x3mm_P0.5mm,C404329,MMC5983MA,1
RV-3028-C7,U23,MicroCrystal_C7_SON-8_1.5x3.2mm_P0.9mm,,RV-3028-C7 32.768kHz 1ppm TA QC,1
MAX-M10S,U24,ublox_MAX,,MAX-M10S-00B,1
"TLP291(GB-TP,SE","U25,U26",SOIC-4_4.55x2.6mm_P1.27mm,C55144,"TLP291(GB-TP,SE",2
12 MHz,Y1,Crystal_SMD_3225-4Pin_3.2x2.5mm,C9002,X322512MSB4SI,1
